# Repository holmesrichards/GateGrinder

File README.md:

# GateGrinder
Kosmo format synth module, 10 cm wide, to generate clocks and act on triggers and gates (called “signals” generally herein).

Signals come from three sources. There is a jack for an external CV input (±12V). There is a pushbutton for manually created gates. Finally, there is an internal clock to produce a stream of square gates. The clock can be switched On or Off and to Slow or Fast rate ranges, and its Rate can be set, on the front panel. (Slow is around 0.14 Hz to 15 Hz, fast is 3.2 Hz to 320 Hz using the specified components.)

If the Resize On/Off switch is set to Off, the OR of these three signal sources is sent to the Out jack. Otherwise the rising edges are used to trigger a one-shot whose output width is controlled by the Resize Narrow/Wide switch and the Width knob, and the resulting signals are sent to Out. Output widths can vary from about a few milliseconds to about 5 seconds.

(And yes, the width can be set to longer than the time between two pulses. It then ignores any pulses that come along until the resized pulse ends.)

The signal at the Out jack also goes to an inverter whose output goes to the ~Out jack. LEDs indicate when Out and ~Out are on. The rising and falling edges of the Out signal are used to generate trigger pulses which go to the On and Off jacks respectively.

So one can invert gates, change the lengths of gates, convert gates to triggers, convert triggers to gates, make a gate clock, make a trigger clock.

Repository at https://github.com/holmesrichards/GateGrinder includes KiCad format schematic, PCB design, and panel design. Latest versions in the repository contain  modifications I have not tested though others have reported they work; see tagged releases for versions I have verified.

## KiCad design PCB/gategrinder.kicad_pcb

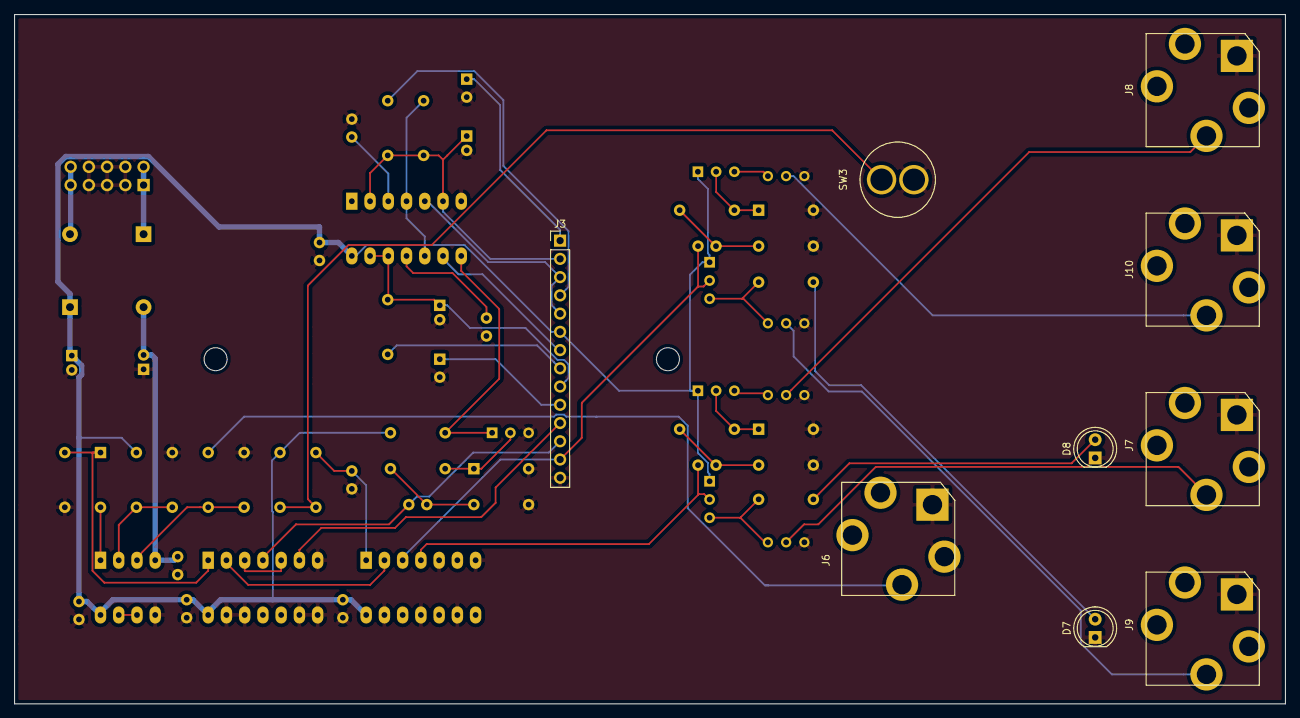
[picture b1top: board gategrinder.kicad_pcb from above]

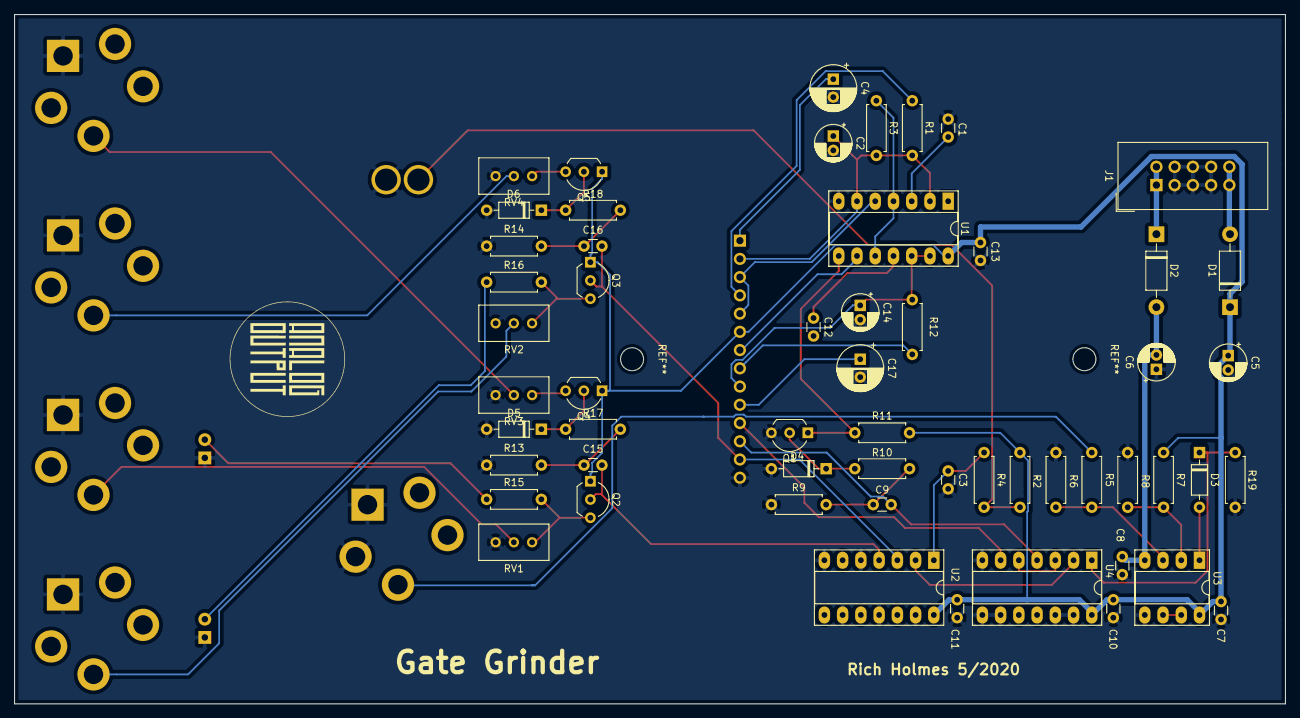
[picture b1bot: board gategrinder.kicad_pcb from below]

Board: 2 copper layers, 177.0 x 96.0 mm, 65 parts (56 on the bottom side), 46 nets.

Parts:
C1, C12: 0.01uF; C_Disc_D3.0mm_W1.6mm_P2.50mm
C2, C14: 2.2uF; CP_Radial_D5.0mm_P2.00mm
C3, C7, C8, C10, C11, C13: 0.1uF; C_Disc_D3.0mm_W1.6mm_P2.50mm
C4, C17: 47uF; CP_Radial_D6.3mm_P2.50mm
C5, C6: 10uF; CP_Radial_D5.0mm_P2.00mm
C9, C15, C16: 100pf; C_Disc_D3.0mm_W1.6mm_P2.50mm
D1, D2: 1N5817; D_DO-41_SOD81_P10.16mm_Horizontal
D3, D4, D5, D6: 1N4148; D_DO-35_SOD27_P7.62mm_Horizontal
D7, D8: LED; LED_D5.0mm
J1: EURO_PWR_2x5; IDC-Header_2x05_P2.54mm_Vertical
J3: Conn_01x14; PinHeader_1x14_P2.54mm_Vertical
J6, J7, J8, J9, J10: AudioJack3_SwitchTR; Jack_6.35mm_PJ_629HAN
Q1, Q2, Q3, Q4, Q5: BC547; TO-92_Inline_Wide
R1, R12: 1k; R_Axial_DIN0207_L6.3mm_D2.5mm_P7.62mm_Horizontal
R2, R5, R6, R7, R9, R10, R13, R14, R17, R18, R19: 100k; R_Axial_DIN0207_L6.3mm_D2.5mm_P7.62mm_Horizontal
R3: 1M; R_Axial_DIN0207_L6.3mm_D2.5mm_P7.62mm_Horizontal
R4, R11: 10k; R_Axial_DIN0207_L6.3mm_D2.5mm_P7.62mm_Horizontal
R8: 15k; R_Axial_DIN0207_L6.3mm_D2.5mm_P7.62mm_Horizontal
R15, R16: RL; R_Axial_DIN0207_L6.3mm_D2.5mm_P7.62mm_Horizontal
RV1, RV2, RV3, RV4: 2k; Potentiometer_Bourns_3296W_Vertical
SW3: SW_Push; Tayda-PBS11-pushbutton
U1: NE556N; DIP-14_W7.62mm_Socket_LongPads
U2: 4069; DIP-14_W7.62mm_Socket_LongPads
U3: TL072; DIP-8_W7.62mm_Socket_LongPads
U4: 4071; DIP-14_W7.62mm_Socket_LongPads

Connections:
/555G2T: C9.2, J3.12, U4.4
/-12V: C6.2, C8.1, D2.2, U3.4
/BUTTON_IN: U2.2, U4.2
/CLOCK_OUT: J3.3, J3.5, U1.5
/CLOCK_RANGE_1: C4.1, J3.1
/CLOCK_RANGE_2: C2.1, J3.2, R1.2, R3.2, U1.2, U1.6
/CLOCK_RATE_2: J3.4, R1.1
/GATE: C16.1, J3.13, Q3.2, U2.3
/GATE_IN: J6.T, R5.2
/GATE_INV: C15.1, Q2.2, U2.4
/GATE_INV_OUT: J7.T, RV1.2
/GATE_LED: D7.2, R16.1
/GATE_OFF: J8.T, RV3.2
/GATE_ON: J10.T, RV4.2
/GATE_OUT: J9.T, RV2.2
/MANUAL_GATE: R2.2, R4.2, SW3.2
/OR_IN: J3.11, U4.6
/RESIZE_OUT: J3.7, U1.9
/RESIZE_RANGE_1: C17.1, J3.10
/RESIZE_RANGE_2: C14.1, J3.9, R12.2, U1.12, U1.13
/RESIZE_WIDTH_2: J3.8, R12.1
/~GATE~_LED: D8.2, R15.1
GND: C1.2, C2.2, C3.2, C4.2, C5.2, C6.1, C7.1, C8.2, C10.1, C11.1, C12.2, C13.2, C14.2, C17.2, D4.2, D5.2, D6.2, D7.1, D8.1, J1.3, J1.4, J1.5, J1.6, J1.7, J1.8, J3.14, J6.S, J6.TN, J7.S, J8.S, J9.S, J10.S, Q1.3, R6.2, R8.2, R9.1, R13.1, R14.1, R19.2, RV1.1, RV2.1, RV3.1, RV4.1, SW3.1, U1.7, U2.5, U2.7, U2.9, U2.11, U2.13, U3.5, U4.7, U4.8, U4.9, U4.12, U4.13
unnamed: C1.1, U1.3
unnamed: C3.1, R4.1, U2.1
unnamed: C9.1, R9.2, R10.1
unnamed: C12.1, U1.11
unnamed: C15.2, R13.2, R17.1
unnamed: C16.2, R14.2, R18.1
unnamed: D1.2, J1.9, J1.10
unnamed: D2.1, J1.1, J1.2
unnamed: D3.1, R19.1, U4.1
unnamed: D3.2, U3.1
unnamed: D4.1, Q1.2, R10.2
unnamed: D5.1, Q4.2, R17.2
unnamed: D6.1, Q5.2, R18.2
unnamed: Q1.1, R11.1, U1.8
unnamed: Q2.3, R15.2, RV1.3
unnamed: Q3.3, R16.2, RV2.3
unnamed: Q4.3, RV3.3
unnamed: Q5.3, RV4.3
unnamed: R5.1, R6.1, U3.3
unnamed: R7.2, R8.1, U3.2
unnamed: U3.6, U3.7
unnamed: U4.3, U4.5
VCC: C5.1, C7.2, C10.2, C11.2, C13.1, D1.1, J3.6, Q2.1, Q3.1, Q4.1, Q5.1, R2.1, R3.1, R7.1, R11.2, U1.4, U1.10, U1.14, U2.14, U3.8, U4.14

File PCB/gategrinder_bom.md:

# gategrinder BOM

Fri 22 May 2020 10:38:55 AM EDT

Generated from schematic by Eeschema 5.1.5-52549c5~84~ubuntu18.04.1

**This is BOM for the main PCB only**

**Component Count:** 64

| Value | Qty | Part | Description | Vendor |
| ----- | --- | ---- | ----------- | ------ |
| C1, C12 | 2 | 0.01uF | Unpolarized capacitor |  |
| C2, C14 | 2 | 2.2uF | Polarized capacitor |  |
| C3, C7, C8, C10, C11, C13 | 6 | 0.1uF | Unpolarized capacitor |  |
| C4, C17 | 2 | 47uF | Polarized capacitor |  |
| C5, C6 | 2 | 10uF | Polarized capacitor |  |
| C9, C15, C16 | 3 | 100pf | Unpolarized capacitor |  |
| D1, D2 | 2 | 1N5817 | 20V 1A Schottky Barrier Rectifier Diode, DO-41 |  |
| D3, D4, D5, D6 | 4 | 1N4148 | 100V 0.15A standard switching diode, DO-35 |  |
| D7, D8 | 2 | LED | Light emitting diode |  |
| J1 | 1 | EURO_PWR_2x5 |  |  |
| J3 | 1 | Conn_01x14 | Generic connector, single row, 01x14, script generated (kicad-library-utils/schlib/autogen/connector/) |  |
| J6, J7, J8, J9, J10 | 5 | AudioJack3_SwitchTR | Audio Jack, 3 Poles (Stereo / TRS), Switched TR Poles (Normalling) |  |
| Q1, Q2, Q3, Q4, Q5 | 5 | BC547 | 0.1A Ic, 45V Vce, Small Signal NPN Transistor, TO-92 |  |
| R1, R12 | 2 | 1k | Resistor |  |
| R2, R5, R6, R7, R9, R10, R13, R14, R17, R18 | 10 | 100k | Resistor |  |
| R3 | 1 | 1M | Resistor |  |
| R4, R11 | 2 | 10k | Resistor |  |
| R8 | 1 | 15k | Resistor |  |
| R15, R16 | 2 | RL* | Resistor |  |
| RV1, RV2, RV3, RV4 | 4 | 2k | Trim-potentiometer |  |
| SW3 | 1 | SW_Push | Push button switch, generic, two pins |  |
| U1 | 1 | NE556N | Dual Precision Timers, DIP-14/SOIC-14/SSOP-14 |  |
| U2 | 1 | 4069 | Hex inverter |  |
| U3 | 1 | TL072 | Dual Low-Noise JFET-Input Operational Amplifiers, DIP-8/SOIC-8 |  |
| U4 | 1 | 4071 | Quad Or 2 inputs |  |  
  
    
  *For R15–R16 use values that give you your desired LED brightness. Try them on a breadboard with your LED and 12V.

  Also needed/recommended:

- 1 IC socket, 8 pin
- 3 IC sockets, 14 pin
- 1 Eurorack style power cable
- 2 knobs (I used MF-A03, Tayda A-1006)
- 4 M3x6mm screws
- 2 spacers, 12 mm, Tayda A-3317
- 4 Mounting screws

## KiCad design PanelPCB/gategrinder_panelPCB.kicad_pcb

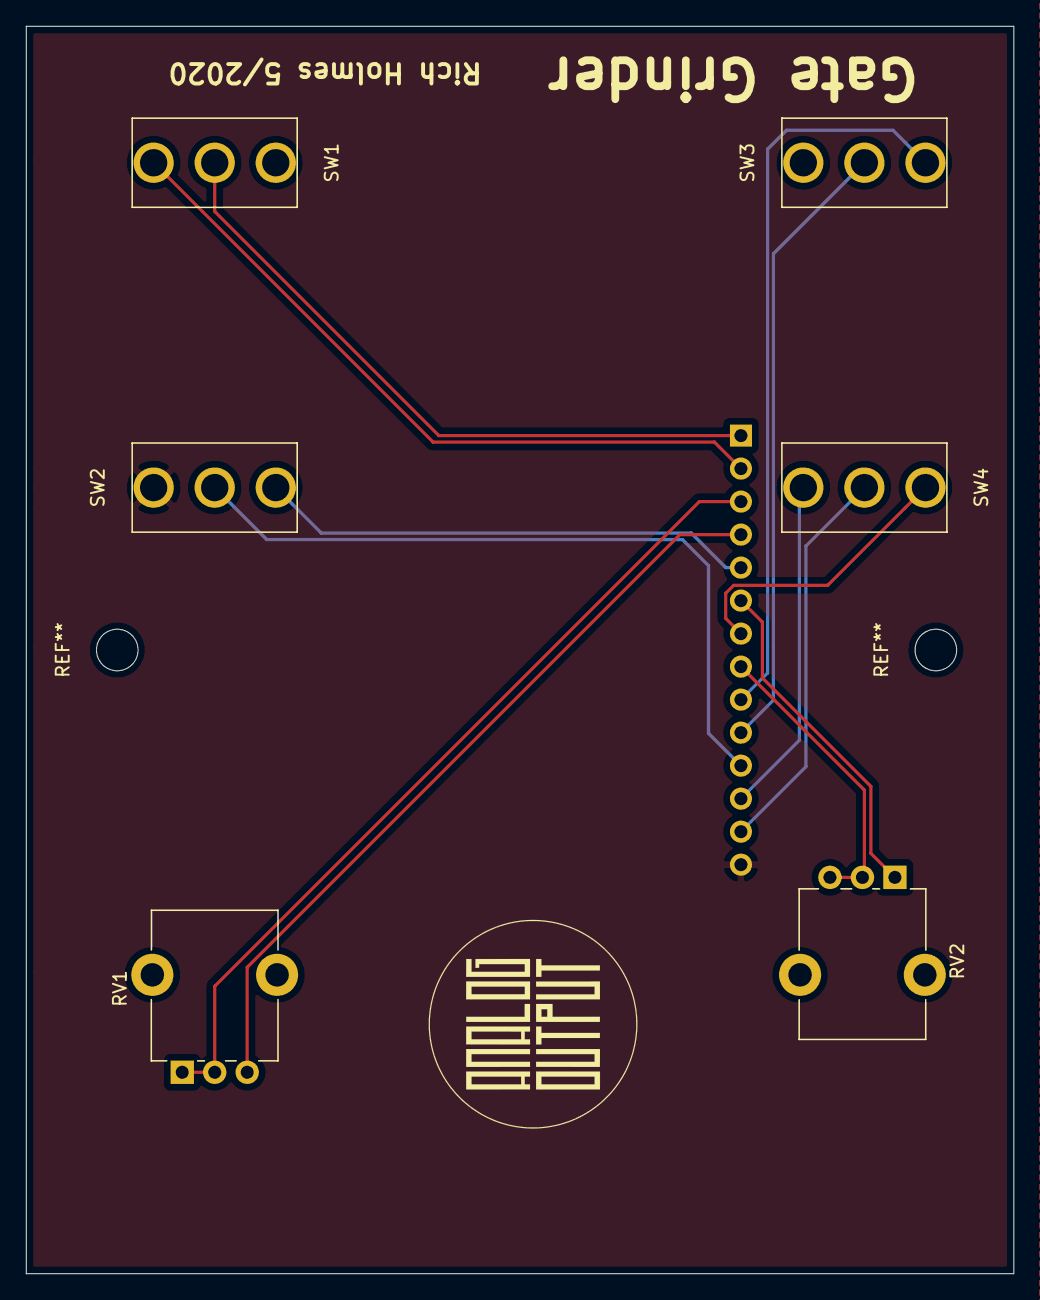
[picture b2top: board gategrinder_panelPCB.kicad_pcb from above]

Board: 2 copper layers, 76.0 x 96.0 mm, 7 parts (1 on the bottom side), 14 nets.

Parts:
J1: Conn_01x14; PinSocket_1x14_P2.54mm_Vertical
RV1, RV2: 100K; Potentiometer_Alpha_RD901F-40-00D_Single_Vertical_CircularH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
SW1, SW3: SW_SPST; SPDT-toggle-switch-1M-series
SW2, SW4: SW_SPDT; SPDT-toggle-switch-1M-series

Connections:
/CLOCK_OUT: J1.5, SW2.1
/CLOCK_RANGE_1: J1.1, SW1.2
/CLOCK_RANGE_2: J1.2, SW1.1
/CLOCK_RATE_1: J1.3, RV1.1, RV1.2
/CLOCK_RATE_2: J1.4, RV1.3
/OR_IN: J1.11, SW2.2
/OR_OUT: J1.12, SW4.1
/OUTPUT: J1.13, SW4.2
/RESIZE_OUT: J1.7, SW4.3
/RESIZE_RANGE_1: J1.10, SW3.2
/RESIZE_RANGE_2: J1.9, SW3.1
/RESIZE_WIDTH_1: J1.6, RV2.1
/RESIZE_WIDTH_2: J1.8, RV2.2, RV2.3
GND: J1.14, SW2.3

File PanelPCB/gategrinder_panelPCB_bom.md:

# gategrinder_panelPCB BOM

Mon 18 May 2020 11:31:23 PM EDT

Generated from schematic by Eeschema 5.1.5-52549c5~84~ubuntu18.04.1

**This is BOM for the panel PCB only**

**Component Count:** 7

| Value | Qty | Part | Description | Vendor |
| ----- | --- | ---- | ----------- | ------ |
| J1 | 1 | Conn_01x14 | Pin socket, female 14 pins |  |
| RV1, RV2 | 2 | 100K | Potentiometer, 9 mm board mount, Tayda A-1848 |  |
| SW1, SW3 | 2 | SW_SPST | Single Pole Single Throw (SPST) switch |  |
| SW2, SW4 | 2 | SW_SPDT | Switch, single pole double throw |  |

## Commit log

2020-02-23 Initial version
2020-02-23 add fp-lib-table
2020-02-23 Create LICENSE
2020-03-01 Panel update
2020-03-01 Fix power header
2020-05-10 Generic adds
2020-05-10 Reorganize, add panel project
2020-05-10 Rotate
2020-05-10 rm old panel attempt
2020-05-10 Libraries cleanup and silkscreen work
2020-05-10 Further cleanup
2020-05-12 Rename panel to panelPCB; final tweaks; Gerbers
2020-05-17 Panel project
2020-05-17 Real first version
2020-05-17 JLCJLCJLCJLC
2020-05-18 Shorten main board; widen transistor footprints
2020-05-18 Standardize names
2020-05-19 No it's not Eurorack, and other updates
2020-05-19 Fix typos
2020-05-19 Panel revision
2020-05-19 BOMs and build notes
2020-05-19 Add image
2020-05-19 Schematics PDFs
2020-05-19 Replace fixed resistor output voltage dividers with trimmers
2020-05-19 Mention use of trimmers
2020-05-22 More V1 files and update current boms
2020-05-22 Note on output resistors
2020-05-26 Consolidated notes for v1
2020-05-26 Letter size
2020-05-26 Correct info on push button
2020-05-31 NA556 -> NE556
    Unless I’m mistaken, this chip is supposed to be the NE556.
2020-05-31 NA556 -> NE556N
2020-06-06 Note on untested modifications
2020-06-13 Added pulldown for OR
2020-06-25 Explain RL
2020-09-01 Gerbers update
2020-11-04 Add R19 to BOM
2020-12-21 README update re verification of mods
2021-01-17 Include lib table files
